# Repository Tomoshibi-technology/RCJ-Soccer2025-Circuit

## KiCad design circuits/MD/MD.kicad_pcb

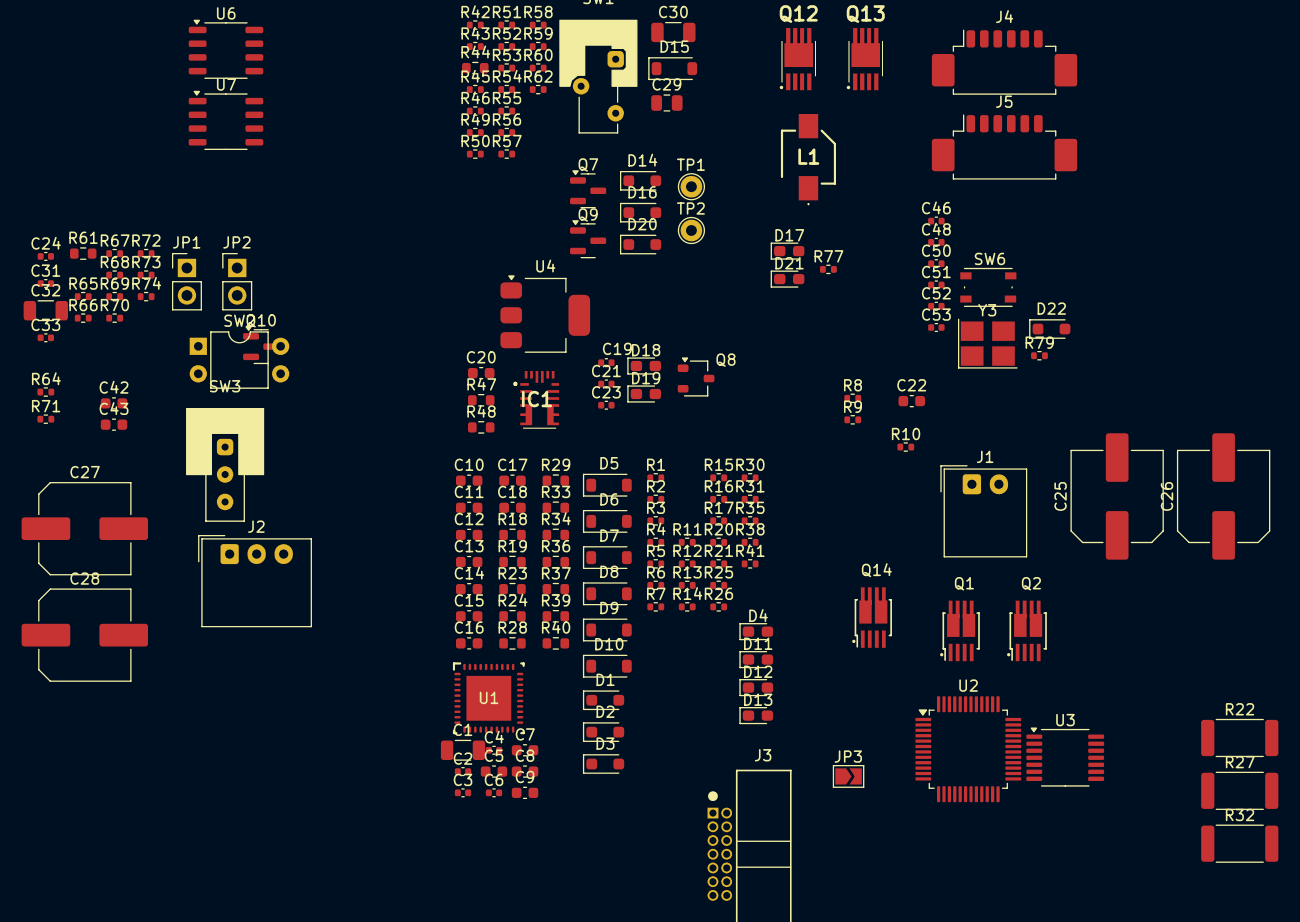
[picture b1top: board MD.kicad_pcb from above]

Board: 2 copper layers, 170 parts (0 on the bottom side), 100 nets, no tracks yet.

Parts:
C1, C30, C32: 10uF; C_1206_3216Metric
C2, C6, C24, C31, C46, C48, C50, C51, C52, C53: 0.1uF; C_0402_1005Metric
C3, C4, C19, C21, C23, C33: 1uF; C_0402_1005Metric
C5: 47nF; C_0603_1608Metric
C7, C8, C9: 330pF; C_0603_1608Metric
C10, C11, C14, C15, C17, C18: CR_snub; C_0603_1608Metric
C12, C13, C16: C_snub; C_0603_1608Metric
C20: 0.1uF; C_0603_1608Metric
C22: 4.7uF; C_0603_1608Metric
C25, C26, C27, C28: 470uF; C_Elec_8x10.2
C29: 22uF; C_0805_2012Metric
C42, C43: 22pF; C_0603_1608Metric
D1, D2, D3, D14, D16, D20, D22: 1N5819WS; D_SOD-323_HandSoldering
D4, D11, D12, D13, D17, D21: Red; LED_0603_1608Metric_Pad1.05x0.95mm_HandSolder
D5, D6, D7, D8, D9, D10, D15: SS2040FL; D_SOD-123
D18, D19: Green; LED_0603_1608Metric_Pad1.05x0.95mm_HandSolder
IC1: DCDC_MPM3620A
J1: Conn_01x02_Male; Molex_SPOX_5268-02A_1x02_P2.50mm_Horizontal
J2: Conn_01x03_Male; Molex_SPOX_5268-03A_1x03_P2.50mm_Horizontal
J3: Conn_01x14_Pin; BoxHeader_2x07_P1.27mm_Horizontal
J4, J5: Conn_01x06_MountingPin; Molex_PicoBlade_53261-0671_1x06-1MP_P1.25mm_Horizontal
JP1, JP2: Jumper_2_Open; PinHeader_1x02_P2.54mm_Vertical
JP3: SolderJumper_2_Open; SolderJumper-2_P1.3mm_Open_TrianglePad1.0x1.5mm
L1: 22uH; Inductor_CDPH4D19F
Q1, Q2, Q14: DMT6017LDV; Package_TSON-Advance_DualFET
Q7, Q9: BSS138; SOT-23
Q8: SSM3J332R; SOT-23W
Q10: S8550; SOT-23
Q12, Q13: DI035P04PT; Package_TSON-Advance
R1, R79: 1k; R_0402_1005Metric
R2, R3, R4, R5, R6, R7, R11, R12, R13, R14, R20, R21, R25, R26, R30, R31, R42, R43, R45, R46, R49, R50, R51, R52, R53, R55, R60, R62, R64, R65, R69, R70, R77: 10k; R_0402_1005Metric
R8, R9, R10, R54: 2k; R_0402_1005Metric
R15, R16, R17: 100; R_0402_1005Metric
R18, R19, R23, R24, R28, R29: 0; R_0603_1608Metric
R22, R27, R32: 7m; R_2512_6332Metric
R33, R34, R36, R37, R39, R40: CR_snub; R_0603_1608Metric
R35, R38, R41, R66: 20k; R_0402_1005Metric
R44: 1k; R_0603_1608Metric
R47: 75k; R_0603_1608Metric
R48: 10k; R_0603_1608Metric
R56: 100k; R_0402_1005Metric
R57: 200k; R_0402_1005Metric
R58: 12k; R_0402_1005Metric
R59, R67, R68, R71, R72: 2.2k; R_0402_1005Metric
R61: 7.5k; R_0603_1608Metric
R73, R74: 120; R_0402_1005Metric
SW1: SW_SPDT_White; SW_Slide_SPDT_White
SW2: SW_DIP_x02; DIP-4_W7.62mm
SW3: SW_SPDT; SW_Slide_3P_SPDT
SW6: SW_SPST; SW_Push_1P1T_NO_Vertical_Wuerth_434133025816
TP1, TP2: TestPoint; TestPoint_THTPad_D2.0mm_Drill1.0mm
U1: Driver_FETGate_DRV8323S
U2: STM32G473CET6; LQFP-48_7x7mm_P0.5mm
U3: Encoder_Magnetic_AS5047P; TSSOP-14_4.4x5mm_P0.65mm
U4: AZ1117CH-3.3; SOT-223-3_TabPin2
U6, U7: MAX3485; SOP-8_3.9x4.9mm_P1.27mm
Y3: 16MHz; Crystal_SMD_3225-4Pin_3.2x2.5mm_HandSoldering

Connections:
+3.3V: C6.1, C22.2, C23.1, C24.1, C28.1, C31.1, C33.2, C46.1, C48.1, C50.1, C52.1, C53.1, D1.1 (K), D2.1 (K), D3.1 (K), D16.2 (A), D22.2 (A), Q10.2 (E), R1.2, R8.2, R13.2, R14.2, R52.2, R67.1, R71.1, SW2.3, SW2.4, SW3.2 (B), TP1.1, U1.24 (VREF), U2.1 (VBAT), U2.20 (VREF+), U2.21 (VDDA), U2.24 (VDD), U2.36 (VDD), U2.48 (VDD), U3.11 (VDD5V), U3.12 (VDD3V), U4.2 (VO), U6.8 (VCC), U7.8 (VCC)
+5V: C21.1, C27.1, D16.1 (K), Q8.3 (D), R9.2, R53.2, U4.3 (VI)
/MotorDriver/Phase_U: C10.1, D5.2 (A), D6.1 (K), J2.1, Q14.3 (S), Q14.7 (D), Q14.8 (D), R20.2, R34.2, R35.1, U1.7 (SHA)
/MotorDriver/Phase_V: C14.1, D7.2 (A), D8.1 (K), J2.2, Q1.3 (S), Q1.7 (D), Q1.8 (D), R25.1, R37.2, R38.1, U1.14 (SHB)
/MotorDriver/Phase_W: C17.1, D9.2 (A), D10.1 (K), J2.3, Q2.3 (S), Q2.7 (D), Q2.8 (D), R30.1, R40.2, R41.1, U1.17 (SHC)
/MotorDriver/SOA: R15.1, U1.23 (SOA)
/MotorDriver/SOB: R16.1, U1.22 (SOB)
/MotorDriver/SOC: R17.1, U1.21 (SOC)
/Power/24VBAT: J1.2, Q13.5 (D)
/Power/PG: IC1.18 (PG), Q9.1 (G), R56.1
/Power/PowerSW: Q7.1 (G), R50.1, R62.2
/Power/S-S: C19.1, Q12.1 (S), Q12.2 (S), Q12.3 (S), Q13.1 (S), Q13.2 (S), Q13.3 (S), R43.1, R45.1, SW1.2 (B)
/RS485/24V_IN: J4.2, JP3.1 (A)
/RS485/24V_OUT: J5.2, JP3.2 (B)
/RS485/RS485_A: J4.3, J5.3, JP1.1 (A), R67.2, U6.6 (A)
/RS485/RS485_B: J4.4, J5.4, R68.1, R73.2, U6.7 (B)
/RS485/RS485_X: J4.5, J5.5, JP2.1 (A), R71.2, U7.6 (A)
/RS485/RS485_Y: J4.6, J5.6, R72.1, R74.2, U7.7 (B)
/UI/DIP_SW0: R69.2, SW2.1
/UI/DIP_SW1: R70.2, SW2.2
/UI/Slide_SW0: R77.1, SW3.1 (A)
BOOT0: R64.1, U2.45 (PB8-BOOT0)
CAL: R12.2, U1.31 (CAL)
Current_OUTA: C9.1, D1.2 (A), R15.2, U2.8 (PA0)
Current_OUTB: C8.1, D2.2 (A), R16.2, U2.9 (PA1)
Current_OUTC: C7.1, D3.2 (A), R17.2, U2.10 (PA2)
ENABLE: R11.2, U1.30 (ENABLE)
GND: C1.2, C2.2, C3.2, C6.2, C7.2, C8.2, C9.2, C11.1, C12.1, C13.1, C15.1, C16.1, C18.1, C20.2, C21.2, C22.1, C23.2, C24.2, C25.2, C26.2, C27.2, C28.2, C29.2, C30.2, C31.2, C32.2, C33.1, C42.1, C43.1, C46.2, C48.2, C50.2, C51.2, C52.2, C53.2, D11.1 (K), D12.1 (K), D13.1 (K), D14.2 (A), D17.1 (K), D18.1 (K), D19.1 (K), D21.1 (K), IC1.3 (AGND), IC1.12 (PGND), IC1.13 (PGND_2), IC1.14 (PGND_3), J1.1, J3.5, J3.7, J3.11, J4.1, J4.MP (MountPin), J5.1, J5.MP (MountPin), Q7.2 (S), Q9.2 (S), R2.1, R3.1, R4.1, R5.1, R6.1, R7.1, R11.1, R12.1, R22.1, R27.1, R32.1, R42.2, R48.2, R49.2, R50.2, R51.2, R52.1, R53.1, R55.2, R59.1, R64.2, R65.2, R66.2, R68.2, R69.1, R70.1, R72.2, R77.2, R79.2, SW6.2 (B), TP2.1, U1.10 (SNA), U1.11 (SNB), U1.20 (SNC), U1.32 (AGND), U1.40 (PGND), U1.41 (PAD), U2.19 (VSSA), U2.23 (VSS), U2.35 (VSS), U2.47 (VSS), U3.5 (TEST), U3.13 (GND), U4.1 (GND), U6.5 (GND), U7.5 (GND), Y3.2, Y3.4
HSE_IN: C42.2, U2.5 (PF0), Y3.1
HSE_OUT: C43.2, U2.6 (PF1), Y3.3
INA_H: R2.2, U1.34 (INHA)
INA_L: R3.2, U1.35 (INLA)
INB_H: R4.2, U1.36 (INHB)
INB_L: R5.2, U1.37 (INLB)
INC_H: R6.2, U1.38 (INHC)
INC_L: R7.2, U1.39 (INLC)
MISO1: R13.1, U1.26 (MODE_SDO), U2.14 (PA6)
MOSI1: U1.27 (IDRIVE_SDI), U2.15 (PA7)
MainRX3_RS485TX: U2.25 (PB11), U6.1 (RO)
MainTX3_RS485RX: R61.2, U2.22 (PB10), U7.4 (DI)
NRST: C51.1, J3.12, SW6.1 (A), U2.7 (NRST)
unnamed: C10.2, R33.1
unnamed: C11.2, R34.1
unnamed: C14.2, R36.1
unnamed: C15.2, R37.1
unnamed: C17.2, R39.1
unnamed: C18.2, R40.1
unnamed: C20.1, R44.2, R47.1
unnamed: D4.2 (A), R1.1
unnamed: D6.2 (A), Q14.1 (S), R21.2, R22.2, U1.9 (SPA)
unnamed: D8.2 (A), Q1.1 (S), R26.1, R27.2, U1.12 (SPB)
unnamed: D10.2 (A), Q2.1 (S), R31.1, R32.2, U1.19 (SPC)
unnamed: D11.2 (A), R35.2
unnamed: D12.2 (A), R38.2
unnamed: D13.2 (A), R41.2
unnamed: D15.1 (K), L1.1
unnamed: D17.2 (A), R54.1
unnamed: D18.2 (A), R9.1
unnamed: D19.2 (A), R8.1
unnamed: C29.1, D20.2 (A), IC1.9 (OUT), Q8.2 (S), R58.2, R60.1
unnamed: D21.2 (A), R10.1
unnamed: D22.1 (K), J3.3, R79.1
unnamed: IC1.17 (EN), R57.1
unnamed: IC1.1 (FB), R58.1, R59.2
unnamed: IC1.2 (VCC), R56.2
unnamed: JP1.2 (B), R73.1
unnamed: JP2.2 (B), R74.1
unnamed: Q1.2 (G), R24.2, R26.2
unnamed: Q1.4 (G), R23.2, R25.2
unnamed: Q2.2 (G), R29.2, R31.2
unnamed: Q2.4 (G), R28.2, R30.2
unnamed: Q7.3 (D), R46.2
unnamed: Q8.1 (G), Q9.3 (D), R60.2
unnamed: Q10.1 (B), R61.1
unnamed: Q10.3 (C), R66.1, U7.2 (~RE), U7.3 (DE)
unnamed: C19.2, Q12.4 (G), R45.2, R46.1
unnamed: Q13.4 (G), R42.1, R43.2
unnamed: Q14.2 (G), R19.2, R21.1
unnamed: Q14.4 (G), R18.2, R20.1
unnamed: R62.1, SW1.1 (A)
unnamed: C5.1, U1.2 (CPH)
unnamed: C5.2, U1.1 (CPL)
unnamed: C3.1, U1.33 (DVDD)
unnamed: R18.1, U1.6 (GHA)
unnamed: R23.1, U1.15 (GHB)
unnamed: R28.1, U1.16 (GHC)
unnamed: R19.1, U1.8 (GLA)
unnamed: R24.1, U1.13 (GLB)
unnamed: R29.1, U1.18 (GLC)
unnamed: C4.2, U1.3 (VCP)
unnamed: R55.1, U2.18 (PB2)
unnamed: R65.1, U6.2 (~RE), U6.3 (DE)
SCLK1: U1.28 (VDS_SCLK), U2.13 (PA5)
SWCLK: J3.6, U2.38 (PA14)
SWDIO: J3.4, U2.37 (PA13)
SWO: J3.8, U2.40 (PB3)
VCC: C26.1, C30.1, D20.1 (K), IC1.16 (IN), L1.2, R51.1, R57.2
VDD: C1.1, C2.1, C4.1, C12.2, C13.2, C16.2, C25.1, C32.1, D5.1 (K), D7.1 (K), D9.1 (K), D14.1 (K), D15.2 (A), Q1.5 (D), Q1.6 (D), Q2.5 (D), Q2.6 (D), Q12.5 (D), Q14.5 (D), Q14.6 (D), R33.2, R36.2, R39.2, R44.1, R49.1, U1.4 (VM), U1.5 (VDRAIN)
V_Meas.: R47.2, R48.1, U2.11 (PA3)
nFAULT: D4.1 (K), R14.1, U1.25 (FAULT_N)

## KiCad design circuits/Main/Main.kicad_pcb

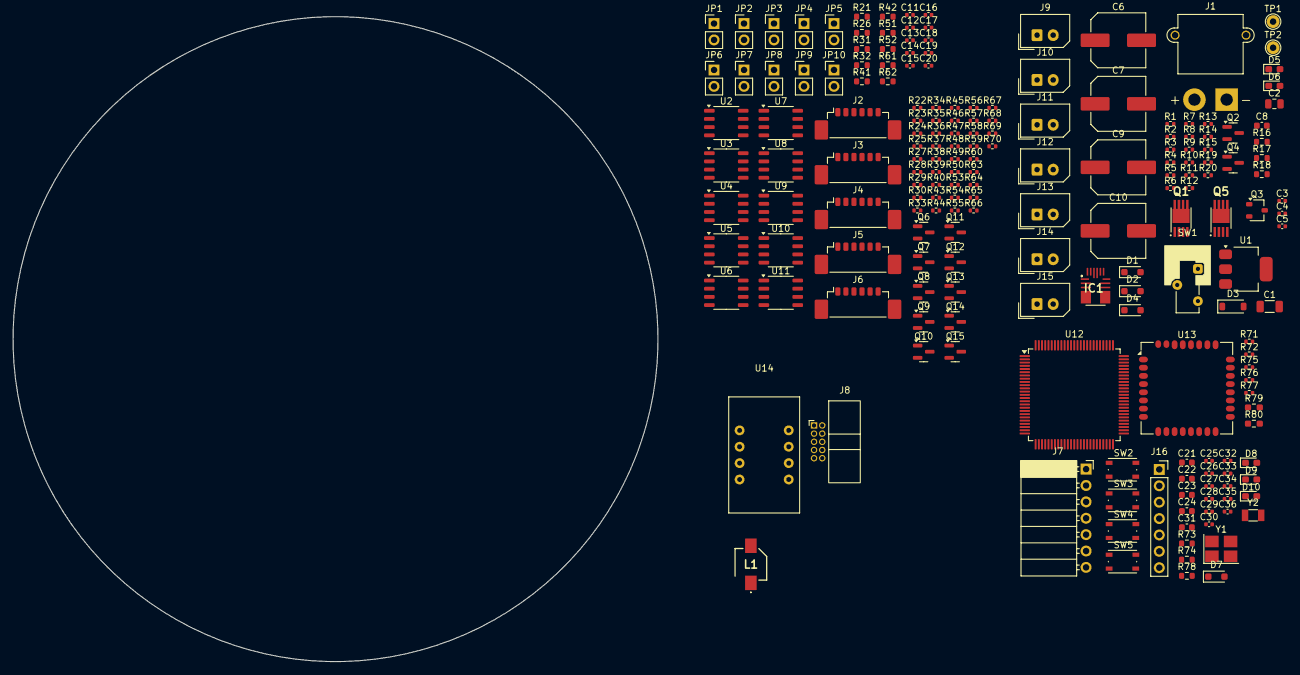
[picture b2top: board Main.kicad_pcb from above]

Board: 2 copper layers, 100.0 x 100.0 mm, 192 parts (0 on the bottom side), 79 nets, no tracks yet.

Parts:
C1: 10uF; C_1206_3216Metric
C2: 22uF; C_0805_2012Metric
C3, C4, C5, C32, C34: 1uF; C_0402_1005Metric
C6, C7, C9, C10: 470uF; C_Elec_8x10.2
C8: 0.1uF; C_0603_1608Metric
C11, C12, C13, C14, C15, C16, C17, C18, C19, C20, C25, C26, C27, C28, C29, C30, C33, C35, C36: 0.1uF; C_0402_1005Metric
C21, C22, C23, C24: 22pF; C_0603_1608Metric
C31: 4.7uF; C_0603_1608Metric
D1, D2, D4, D7: 1N5819WS; D_SOD-323_HandSoldering
D3: SS2040FL; D_SOD-123
D5, D6: Green; LED_0603_1608Metric_Pad1.05x0.95mm_HandSolder
D8, D9, D10: Red; LED_0603_1608Metric_Pad1.05x0.95mm_HandSolder
IC1: DCDC_MPM3620A
J1: Conn_01x02_Male; AMASS_XT30PW-M_1x02_P2.50mm_Horizontal
J2, J3, J4, J5, J6: Conn_01x06_MountingPin; Molex_PicoBlade_53398-0671_1x06-1MP_P1.25mm_Vertical
J7: Conn_01x07_Female; PinSocket_1x07_P2.54mm_Horizontal
J8: Conn_01x10_Male; BoxHeader_2x05_P1.27mm_Horizontal
J9, J10, J11, J12, J13, J14, J15: Conn_01x02_Male; Molex_SPOX_5267-02A_1x02_P2.50mm_Vertical
J16: Conn_01x07_Socket; PinSocket_1x07_P2.54mm_Vertical
JP1, JP2, JP3, JP4, JP5, JP6, JP7, JP8, JP9, JP10: Jumper_2_Open; PinHeader_1x02_P2.54mm_Vertical
L1: 22uH; Inductor_CDPH4D19F
Q1, Q5: DI035P04PT; Package_TSON-Advance
Q2, Q4: BSS138; SOT-23
Q3: SSM3J332R; SOT-23W
Q6, Q7, Q8, Q9, Q10, Q11, Q12, Q13, Q14, Q15: S8050; SOT-23
R1, R2, R7, R8, R9, R10, R11, R12, R13, R14, R15, R71, R72: 10k; R_0402_1005Metric
R3: 200k; R_0402_1005Metric
R4: 100k; R_0402_1005Metric
R5: 12k; R_0402_1005Metric
R6, R23, R24, R28, R29, R35, R36, R37, R38, R45, R46, R47, R48, R55, R56, R57, R58, R65, R66, R67, R68: 2.2k; R_0402_1005Metric
R16: 1k; R_0603_1608Metric
R17: 75k; R_0603_1608Metric
R18: 10k; R_0603_1608Metric
R19, R20, R75, R76, R77: 1k; R_0402_1005Metric
R21, R26, R31, R32, R41, R42, R51, R52, R61, R62: 7.5k; R_0603_1608Metric
R22, R27, R33, R34, R43, R44, R53, R54, R63, R64: 20k; R_0402_1005Metric
R25, R30, R39, R40, R49, R50, R59, R60, R69, R70: 120; R_0402_1005Metric
R73, R74, R78: PullUP?; R_0603_1608Metric
R79, R80: PullUP; R_0603_1608Metric_Pad0.98x0.95mm_HandSolder
SW1: SW_SPDT_White; SW_Slide_SPDT_White
SW2, SW3, SW4, SW5: SW_SPST; SW_Push_1P1T_NO_Vertical_Wuerth_434133025816
TP1, TP2: TestPoint; TestPoint_THTPad_D2.0mm_Drill1.0mm
U1: AZ1117CH-3.3; SOT-223-3_TabPin2
U2, U3, U4, U5, U6, U7, U8, U9, U10, U11: MAX3485; SOP-8_3.9x4.9mm_P1.27mm
U12: STM32F446VETx; LQFP-100_14x14mm_P0.5mm
U13: TWE-L-WX; MonoWireless_TWE-L-WX
U14: BNO055; Sensor_Motion_Aktk_BNO055
Y1: 16MHz; Crystal_SMD_3225-4Pin_3.2x2.5mm_HandSoldering
Y2: 32.768kHz; Crystal_SMD_3215-2Pin_3.2x1.5mm

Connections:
+3.3V: C5.1, C10.1, C11.1, C12.1, C13.1, C14.1, C15.1, C16.1, C17.1, C18.1, C19.1, C20.1, C25.1, C26.1, C27.1, C29.1, C30.1, C32.1, C34.2, C35.1, D4.2 (A), Q6.2 (E), Q7.2 (E), Q8.2 (E), Q9.2 (E), Q10.2 (E), Q11.2 (E), Q12.2 (E), Q13.2 (E), Q14.2 (E), Q15.2 (E), R15.2, R20.2, R23.1, R28.1, R35.1, R37.1, R45.1, R47.1, R55.1, R57.1, R65.1, R67.1, R73.1, R74.1, R78.2, R79.1, R80.1, SW2.2 (B), TP1.1, U1.2 (VO), U2.8 (VCC), U3.8 (VCC), U4.8 (VCC), U5.8 (VCC), U6.8 (VCC), U7.8 (VCC), U8.8 (VCC), U9.8 (VCC), U10.8 (VCC), U11.8 (VCC), U13.5 (VCC), U14.3 (VDD)
+5V: C4.1, C9.1, D4.1 (K), Q3.3 (D), R10.2, R19.2, U1.3 (VI)
/3.3VBUS: C36.1, J8.1
/Power/24VBAT: J1.2, Q1.5 (D)
/Power/PG: IC1.18 (PG), Q2.1 (G), R4.1
/Power/S-S: C3.1, Q1.1 (S), Q1.2 (S), Q1.3 (S), Q5.1 (S), Q5.2 (S), Q5.3 (S), R9.1, R11.1, SW1.2 (B)
/Power/V_Measure: R17.2, R18.1
/Power/Vfb: C2.1, D1.2 (A), IC1.9 (OUT), Q3.2 (S), R5.2, R8.1
BOOT0: R71.1, SW2.1 (A)
GND: C1.2, C2.2, C4.2, C5.2, C6.2, C7.2, C8.2, C9.2, C10.2, C11.2, C12.2, C13.2, C14.2, C15.2, C16.2, C17.2, C18.2, C19.2, C20.2, C21.1, C22.1, C23.1, C24.1, C25.2, C26.2, C27.2, C28.2, C29.2, C30.2, C31.1, C32.2, C33.2, C34.1, C35.2, C36.2, D2.2 (A), D5.1 (K), D6.1 (K), D8.1 (K), D9.1 (K), D10.1 (K), IC1.3 (AGND), IC1.12 (PGND), IC1.13 (PGND_2), IC1.14 (PGND_3), J1.1, J7.1, J8.4, Q2.2 (S), Q4.2 (S), R2.2, R6.1, R7.2, R10.1, R13.2, R14.2, R15.1, R18.2, R22.2, R24.2, R27.2, R29.2, R33.2, R34.2, R36.2, R38.2, R43.2, R44.2, R46.2, R48.2, R53.2, R54.2, R56.2, R58.2, R63.2, R64.2, R66.2, R68.2, R71.2, R72.2, SW3.2 (B), SW4.2 (B), SW5.2 (B), TP2.1, U1.1 (GND), U2.5 (GND), U3.5 (GND), U4.5 (GND), U5.5 (GND), U6.5 (GND), U7.5 (GND), U8.5 (GND), U9.5 (GND), U10.5 (GND), U11.5 (GND), U13.20 (GND), U13.22 (ADC2/AI3), U13.23 (ADC1/AI1), U13.28 (GND), U13.30 (GND), U13.31 (GND), U13.32 (GND), U14.2 (GND), Y1.2, Y1.4
HSE_IN: C21.2, Y1.1
HSE_OUT: C22.2, Y1.3
I2C1_SCL: R80.2, U14.19 (COM1)
I2C1_SDA: R79.2, U14.20 (COM0)
LSE_IN: C23.2, Y2.2
LSE_OUT: C24.2, Y2.1
MainRX6_RS485aTX: U2.1 (RO), U3.1 (RO), U4.1 (RO), U5.1 (RO), U6.1 (RO), U7.1 (RO), U8.1 (RO), U9.1 (RO), U10.1 (RO), U11.1 (RO)
MainTX6_RS485aRX: R21.2, R26.2, R31.2, R32.2, R41.2, R42.2, R51.2, R52.2, R61.2, R62.2, U2.4 (DI), U3.4 (DI), U4.4 (DI), U5.4 (DI), U6.4 (DI), U7.4 (DI), U8.4 (DI), U9.4 (DI), U10.4 (DI), U11.4 (DI)
NRST: C28.1, J8.6, SW3.1 (A)
unnamed: C8.1, R16.2, R17.1
unnamed: D3.1 (K), L1.1
unnamed: D5.2 (A), R19.1
unnamed: D6.2 (A), R20.1
unnamed: D8.2 (A), R75.1
unnamed: D9.2 (A), R76.1
unnamed: D10.2 (A), R77.1
unnamed: IC1.17 (EN), R3.1
unnamed: IC1.1 (FB), R5.1, R6.2
unnamed: IC1.2 (VCC), R4.2
unnamed: JP1.2 (B), R25.1
unnamed: JP2.2 (B), R30.1
unnamed: JP3.2 (B), R39.1
unnamed: JP4.2 (B), R40.1
unnamed: JP5.2 (B), R49.1
unnamed: JP6.2 (B), R50.1
unnamed: JP7.2 (B), R59.1
unnamed: JP8.2 (B), R60.1
unnamed: JP9.2 (B), R69.1
unnamed: JP10.2 (B), R70.1
unnamed: Q1.4 (G), R7.1, R9.2
unnamed: Q2.3 (D), Q3.1 (G), R8.2
unnamed: Q4.3 (D), R12.2
unnamed: C3.2, Q5.4 (G), R11.2, R12.1
unnamed: Q6.1 (B), R21.1
unnamed: Q6.3 (C), R22.1, U2.2 (~RE), U2.3 (DE)
unnamed: Q7.1 (B), R26.1
unnamed: Q7.3 (C), R27.1, U3.2 (~RE), U3.3 (DE)
unnamed: Q8.1 (B), R31.1
unnamed: Q8.3 (C), R33.1, U4.2 (~RE), U4.3 (DE)
unnamed: Q9.1 (B), R32.1
unnamed: Q9.3 (C), R34.1, U5.2 (~RE), U5.3 (DE)
unnamed: Q10.1 (B), R41.1
unnamed: Q10.3 (C), R43.1, U6.2 (~RE), U6.3 (DE)
unnamed: Q11.1 (B), R42.1
unnamed: Q11.3 (C), R44.1, U7.2 (~RE), U7.3 (DE)
unnamed: Q12.1 (B), R51.1
unnamed: Q12.3 (C), R53.1, U8.2 (~RE), U8.3 (DE)
unnamed: Q13.1 (B), R52.1
unnamed: Q13.3 (C), R54.1, U9.2 (~RE), U9.3 (DE)
unnamed: Q14.1 (B), R61.1
unnamed: Q14.3 (C), R63.1, U10.2 (~RE), U10.3 (DE)
unnamed: Q15.1 (B), R62.1
unnamed: Q15.3 (C), R64.1, U11.2 (~RE), U11.3 (DE)
unnamed: R1.1, SW1.1 (A)
unnamed: U12.10 (VSS), U12.27 (VSS), U12.49 (VSS), U12.74 (VSS), U12.99 (VSS)
unnamed: R78.1, U13.1 (DO0/PWM2)
PRG: J7.3, R74.2, SW5.1 (A), U13.2 (DO1/PWM3)
RS485a_A: JP1.1 (A), JP2.1 (A), JP3.1 (A), JP4.1 (A), JP5.1 (A), JP6.1 (A), JP7.1 (A), JP8.1 (A), JP9.1 (A), JP10.1 (A), R23.2, R28.2, R35.2, R37.2, R45.2, R47.2, R55.2, R57.2, R65.2, R67.2, U2.6 (A), U3.6 (A), U4.6 (A), U5.6 (A), U6.6 (A), U7.6 (A), U8.6 (A), U9.6 (A), U10.6 (A), U11.6 (A)
RS485a_B: R24.1, R25.2, R29.1, R30.2, R36.1, R38.1, R39.2, R40.2, R46.1, R48.1, R49.2, R50.2, R56.1, R58.1, R59.2, R60.2, R66.1, R68.1, R69.2, R70.2, U2.7 (B), U3.7 (B), U4.7 (B), U5.7 (B), U6.7 (B), U7.7 (B), U8.7 (B), U9.7 (B), U10.7 (B), U11.7 (B)
RST: C33.1, D7.2 (A), J7.5, R73.2, SW4.1 (A), U13.21 (~RESET)
SET: J7.7, U13.13 (DIO12/DI1)
TweWriteRX_TweTX0: J7.2, U13.8 (DIO6/TX)
TweWriteTX_TweRX0: J7.4, U13.9 (DIO7/RX)
Twe_LED0: R75.2, U13.19 (DIO17/BPS)
Twe_LED1: R76.2, U13.18 (DIO16/DI4)
Twe_LED2: R77.2, U13.16 (DIO11/DI3)
VCC: C1.1, C7.1, D1.1 (K), IC1.16 (IN), L1.2, R3.2, R14.1
VDD: C6.1, D2.1 (K), D3.2 (A), Q5.5 (D), R13.1, R16.1
主電源スイッチ: Q4.1 (G), R1.2, R2.1

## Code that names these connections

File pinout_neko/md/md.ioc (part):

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Mcu.Name=STM32G473C(B-C-E)Tx
Mcu.Package=LQFP48
Mcu.UserName=STM32G473CETx
PA0.Mode=IN1-Differential
PA0.Signal=ADC1_IN1
PA1.Mode=IN1-Differential
PA1.Signal=ADC1_IN2
PA10.Signal=S_TIM1_CH3
PA11.Signal=S_TIM1_CH4
PA13.Signal=SYS_JTMS-SWDIO
PA14.Signal=SYS_JTCK-SWCLK
PA2.Mode=IN3-Differential
PA2.Signal=ADC1_IN3
PA3.Mode=IN3-Differential
PA3.Signal=ADC1_IN4
PA5.Signal=SPI1_SCK
PA6.Signal=SPI1_MISO
PA7.Signal=SPI1_MOSI
PA8.Signal=S_TIM1_CH1
PA9.Signal=S_TIM1_CH2
PB10.Signal=USART3_TX
PB11.Signal=USART3_RX
PB3.Signal=SYS_JTDO-SWO
PB4.Signal=S_TIM3_CH1
PB5.Signal=S_TIM3_CH2
PF0-OSC_IN.Mode=HSE-External-Oscillator
PF0-OSC_IN.Signal=RCC_OSC_IN
PF1-OSC_OUT.Mode=HSE-External-Oscillator
PF1-OSC_OUT.Signal=RCC_OSC_OUT
RCC.HSE_VALUE=16000000
RCC.SYSCLKFreq_VALUE=170000000
RCC.SYSCLKSource=RCC_SYSCLKSOURCE_PLLCLK
board=custom

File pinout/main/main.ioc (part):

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Mcu.Name=STM32F446V(C-E)Tx
Mcu.Package=LQFP100
Mcu.UserName=STM32F446VETx
PA1.Mode=Asynchronous
PA1.Signal=UART4_RX
PA10.Mode=Asynchronous
PA10.Signal=USART1_RX
PA13.Mode=Trace_Asynchronous_SW
PA13.Signal=SYS_JTMS-SWDIO
PA14.Mode=Trace_Asynchronous_SW
PA14.Signal=SYS_JTCK-SWCLK
PA2.Mode=Asynchronous
PA2.Signal=USART2_TX
PA3.Mode=Asynchronous
PA3.Signal=USART2_RX
PA4.Signal=COMP_DAC1_group
PA5.Mode=Full_Duplex_Master
PA5.Signal=SPI1_SCK
PA6.Mode=Full_Duplex_Master
PA6.Signal=SPI1_MISO
PA7.Mode=Full_Duplex_Master
PA7.Signal=SPI1_MOSI
PA9.Mode=Asynchronous
PA9.Signal=USART1_TX
PB3.Mode=Trace_Asynchronous_SW
PB3.Signal=SYS_JTDO-SWO
PB6.Mode=I2C
PB6.Signal=I2C1_SCL
PB7.Mode=I2C
PB7.Signal=I2C1_SDA
PC10.Mode=Asynchronous
PC10.Signal=UART4_TX
PC6.Mode=Asynchronous
PC6.Signal=USART6_TX
PC7.Mode=Asynchronous
PC7.Signal=USART6_RX
PD8.Mode=Asynchronous
PD8.Signal=USART3_TX
PD9.Mode=Asynchronous
PD9.Signal=USART3_RX
PE7.Mode=Asynchronous
PE7.Signal=UART5_RX
PE8.Mode=Asynchronous
PE8.Signal=UART5_TX
PH0-OSC_IN.Mode=HSE-External-Oscillator
PH0-OSC_IN.Signal=RCC_OSC_IN
PH1-OSC_OUT.Mode=HSE-External-Oscillator
PH1-OSC_OUT.Signal=RCC_OSC_OUT
board=custom

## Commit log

2024-10-17 プロジェクト作成
2024-10-18 あるていど
2024-10-19 mdできた
2024-10-20 mainやった
2024-10-20 cameraできた
2024-10-20 uiとboostもできた
2024-10-21 こみっと
2024-10-22 とちゅう
2024-11-15 gitignore追加
